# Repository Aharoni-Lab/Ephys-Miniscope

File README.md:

## Tutorial for assembling and using the integrated ephys Miniscope

Here we discuss the setup for the E-Scope. Below outlines the steps involved in assembling the head-mounted portion and DAQ portion of the system.

## Head-mounted E-Scope soldering and assembly

#### Components that need to be bought

* [Atmel ICE](https://www.digikey.com/products/en?mpart=ATATMEL-ICE&v=150) for programming the wire-free PCB
* Mill-Max 50mil male and female headers. You can get these from digikey.com and they are used to connect the INTAN PCB to the CMOS PCB. These are optional and generally should be skipped for mice.

#### Software to download
* Download [Atmel Studio](https://www.microchip.com/mplab/avr-support/atmel-studio-7). This will be used to program the microcontroller firmware onto the CMOS PCB.
* Downloaod the [Intan RHD2000 Interface Software](http://intantech.com/files/RHD2000interface_compiled_v1_5_2.zip). This will be used to connect and record ephys data.

### 1) Soldering wires to connect the CMOS PCB to the INTAN PCB

We first need to wire up 5 wires on the CMOS PCB. You should use very thing wiring for this (~0.25mm diameter conductors) since some of these connections will attach directly to the side pad of the serializer chip. You can use very thing "wire-wrap" wire which is single core or you can use mutlicore wire. Single core has the advantage of not splaying out but it is also less flexible. Once soldered, you should lay all 5 wires down across the top of the serializer and epoxy them (with a PCB safe glue/epoxy) so that no strain is applied to the solder connections. 

Below is a picture of the locations to solder the 5 wires. 
* D10 and D11 will carry the SSC Clock and SSC Data lines. 
* PCLK carries the pixel clock which will drive the SSC data protocol out of the INTAN PCB. 
* Finally, V+ and GND will provide power to the INTAN PCB.

### 2) Soldering wires onto the INTAN PCB

Now we need to solder the wires coming off the CMOS PCB onto the INTAN PCB. We have the choice to either directly solder these wires or to place a MillMax 50mil pitch header on these pads to connectorize them. For mice I would suggest directly soldering to minimize size and weight.

For connecting to the CMOS PCB v3.2 you will do the following connections (shown in the image below:
* GND connects to GND
* MCU V+ connects to V+
* INTAN V+ connects to V+
* SSC DATA connects to D10 or D11 (either is fine but keep this consistent across the E-Scopes you assemble
* LV can be left unconnected
* SSC Clock connects to PCLK
* SSC FRAME connects to D10 or D11 (use which ever one you didn't connect SSC DATA to)

### 3) Programming the MCU on the INTAN PCB

On one side of the INTAN PCB is the Intan RHD2132 chip and the other side is an ARM Cortex microcontroller (MCU). This MCU needs to be programmed once with the E-Scope firmware before it is functional. To do this we need to connect 4 lines to the INTAN PCB. This can, and maybe should, be done before completing step 2 above. The advantage of doing this programming step after completing step 2 above is the INTAN PCB can be powered through the coax cable and no additional power supply is needed.

You need to connect the following lines (refer to the images in step 2):
* SWCLK
* SWDIO
* MCU V+
* GND

These 4 lines need to be connected to an Atmel ICE which is the hardware necessary to program the MCU using an SWD protocol.
* In order to program the microcontroller on the INTAN  PCB, we first need to wire-up and connectorize a 4pin Mill-Max header to the 4 programming pins of the Atmel ICE programmer. These are GND, VTG (or V+), SWDIO, and SWDCLK. Below shows which pins/wires of the Atmel ICE have which function. The Atmel ICE has 2 different 5x2 pin ports. One is labeled AVR and one is labeled SAM. Either will work but depending on which one you are using it will change which column you refer to in the below chart.

* Connect the Atmel ICE to the programming header of the INTAN PCB.
* Power up the INTAN PCB throught either the coax cable (using the Miniscope DAQ) or directly connect 3.3V and GND from a power supply to the V+ and GND pads. 
* When the INTAN PCB gets powered on, you should see an orange light turn on on the Atmel ICE which shows that the Atmel ICE has detected voltage on the VTG (Voltage Target) pin.
* Open Atmel Studio and click the "Device Programming" button

* In the Device Programming window that pops up select:
  * Tool: Atmel ICE
  * Device: ATSAM....
  * Interface: SWD
  * Then click "Apply"
* Now check to make sure that Atmel Studio can communicate with the microcontroller on the INTAN PCB. You do this by clicking the "Read" button under Device Signature. If everything is powered and connected correctly you should see some numbers and letter pop up in the box and no error window show up. Now we are ready to program the microcontroller.
* Exit the Device Programming window.
* Now we have to do something a bit weird. I am not sure why this has to be done but it does. Open up the Atmel project found in the "/E-Scope-firmware" folder. This load up the code that makes up the INTAN MCU firmware. Now click "Debug" from the top menu bar and then click "Start Debugging and Break". Wait about 15 seconds while the debugger does its thing in Atmel Studio and then the code should jump to the "main()" function and highlight it. Now click the play button (labelled "Start Debugging") in the top menu. Wait a few seconds then click the stop button (labelled "Stop Debugging"). 
* Go back to the "Device Programming" window by clicking the "Device Programming" button.
* Click "Memory" on the left menu panel of the Device Programming window we are currently in.
* Click "Browse" and locate the E-Scope firmware. This is a .hex file you can find in the "/E-Scope-firmware" folder.
* Click "Program". This will erase, program, and verify the microcontroller. It will tell you if everything was successful.
* Now the microcontroller on the INTAN PCB knows how to be a wire-free Miniscope microcontroller.

## Miniscope DAQ E-Scope soldering and assembly

We now need to modify the standard Miniscope DAQ to be able to handle and transmit the ephys data from the E-Scope. We will do this by soldering 4 wires onto the DAQ PCB which will send the ephys data from the Miniscope DAQ to our SSC to INTAN LVDS PCB. We will roughly be following the following schematic:

As you can see from the schematic, these wires coming off of the Miniscope DAQ PCB will connect to hardware that basically undoes the SSC data protocol implemented by the MCU on the INTAN PCB and make an Intan DAQ think that it is talking directly to an Intan headstage.

### 1) Wire up the Miniscope DAQ PCB

Similar to what we did for wiring up the CMOS PCB, we need to wire up some lines for SSC DATA, SSC Clock, SSC FRAME, and power. See image below for which pads to solder to. Use the same wire as you used to wire up the CMOS PCB and epoxy these wires down to the DAQ PCB to remove any strain on the solder joints.

You definitely need to solder up D10, D11, PCLK, and GND. The need for the 3.3V connection will depend on which version of the system you are using. You might as well just solder this one up as well.

### 2) Change the Miniscope DAQ Deserializer Mode from 10 bits to 12 bits

We need to remove one resistor on the Miniscope PCB and short then now empty pads together . This resistor is responsible for change the Deserializer from using 10bit mode to 12bit mode. We need to do this because the CMOS imaging sensor uses the bottom 10 bits of the SERDES and the Ephys data uses the top 2 bits (TD, TF which are on pins D10 and D11). So **remove resistor R46 (which is circled in yellow above)** which is near the top of the PCB to the right of the SMA connector that goes to the head-mounted scope. Once you remove this resistor, we need to short the 2 open pads together which effectively changes this resistance to 0 ohms. You can build up a solder ball that spans these 2 pads, solder a short piece of metal across these 2 pads, or solder a 0ohm resistor in the R46 location. I recommend the last option.

### 3) Connect the Miniscope DAQ PCB to SSC-2-INTAN-LVDS PCB

Alright, we are almost done here. The ephys data coming out of the wires we soldered onto the Miniscope DAQ need to get converted to a data protocol an Intan DAQ understands. We do this using our custom SSC-2-INTAN-LVDS PCB. This PCB receives SSC (RF,RT,RK) and converts it to an LVDS SPI to be sent out over a 2x6 omnetics connector at the top of the PCB to an Intan or OpenEphys DAQ. Below is a rendering of this PCB.

At the bottom of this board is a 5 pin 100mil pitch header for connecting it to the Miniscope DAQ. I would suggest soldering a right angle header to this PCB pointing down. On the Miniscope DAQ, you can epoxy another 5 pin header to the edge of the PCB so that these 2 PCBs can be easily connected. The connections need to be the following:

**NOTE**

**For the original version of this PCB, the labelling is incorrect.** The order should 3.3V, RD, RF, RK, GND and not 3.3V, RK, RD, RF, GND.

| SSC-2-INTAN PCB | Miniscope DAQ PCB |
| --- | --- |
| GND | GND |
| 3.3V | 3.3V |
| RK | PCLK |
| RD | D10 or D11. Whichever one was connected to TD on the 32 channel Ephys PCB|
| RF | D10 or D11. Whichever one was connected to TF on the 32 channel Ephys PCB |

### 4) Program the MCU on the SSC-2-INTAN-LVDS PCB

Out last step is to program this PCB so it knows what it is suppose to do. Here we follow the same procedure we did above for programming the 32 Channel Ephys PCB. The programming header on the SSC-2-INTAN-LVDS PCB is on the left and includes the 4 connections you need access to through a 100mil pitch header. These are VTG (which will tell the Atmel ICE programmer to program the MCU at 3.3V), SWDIO, SWCLK, and GDN. Follow the steps above but program this MCU with the SSC-2-INTAN-LVDS firmware .hex file. This PCB needs to be powered up when programming which is done through the bottom 'MS-DAQ' 5 pin header by supplying 3.3V and GND. If you already have this hooked up to the Miniscope DAQ all you should need to do is power up the Miniscope DAQ and it should in turn power on this PCB.

## Hook everything up and test the system

We should now be done with all the hard work. All that is left to do is connect everything together and make sure we are getting correct data from the system. The overall layout should be:

32 Channel Ephys PCB -> CMOS sensor PCB -> coax -> Miniscope DAQ -> SSC-2-INTAN-LVDS PCB -> Intan or Open Ephys DAQ

All the power on all of these PCBs is floating which apperently introduces a ton of noise. **To fix this we need to connect building ground to the ground of the Miniscope system. This can be most easily done (be careful) by plugging in only the ground pin of an electrical cord into a wall electical socket and then clip the other end of the ground wire of the cable to the pin labeled 'GND' on the SSC-2-INTAN-LVDS PCB. Do this before powering everything up.**

Once you have connected building ground you can plug in the USB cable of the Miniscope DAQ and the USB cable and power jack of the Intan DAQ. Now open up the Intan DAQ software on the computer and make sure it detects the Intan DAQ and a 32 channel headstage. Right now the Intan DAQ thinks it is talking to an Intan headstage but it is actually talking to the SSC-2-INTAN-LVDS PCB. If you leave the coax cable unconnected from the Miniscope DAQ you will see placeholder data show up in the Intan DAQ software. This should look like DC voltages on all 32 channels with channel 0 having the lowest voltage and channel 31 having the highests. Once the head-mounted Miniscope coax cable is connected, this placeholder data gets replaced with real ephys data.

**A few important notes:**

* Generally you will want the ephys and imaging synced together. This is done by connecting one of the Intan DAQ digital input ports to the SYNC output of the Miniscope DAQ (which is the SMA connector labeled J5). Make sure to enable this digitial input pin in the Intan DAQ software. This will result in the Intan DAQ recording the SYNC signal from the Miniscope DAQ which will allow us to sync all the data offline. If you do this, **make sure to always start the Intan DAQ software recordinging before you start the Miniscope DAQ software recording.**

**Order of connecting and powering up the system**

* Hook up ground of the DAQ system to building ground
* Connect the Miniscope to Miniscope DAQ using the coax cable
* Hook up the DC power supply on the Intan DAQ
* Hook up the two USB cables. One for the Miniscope DAQ and one for the Intan DAQ
* Make sure that the sync cable is connected (Cable that connects the Intan board with the Miniscope DAQ)
* Open up Intan DAQ software and Miniscope DAQ software
* In the Intan software, click "Board Digital Inputs" radio button. Then turn on LOGIC DIN-00.
* Check everything is running correctly by clicking the "Runn" button in the Intan software and by connecting to the Miniscope using the Miniscope DAQ software.

**When ready to record**
* In the Intan software, click the "Select Vase Filename" button and name the ephys recording file.
* Click record in the Intan software
* Click record in the Miniscope DAQ software
* Do your recording
* Stop recording with the Miniscope DAQ software
* Stop recording with the Intan software

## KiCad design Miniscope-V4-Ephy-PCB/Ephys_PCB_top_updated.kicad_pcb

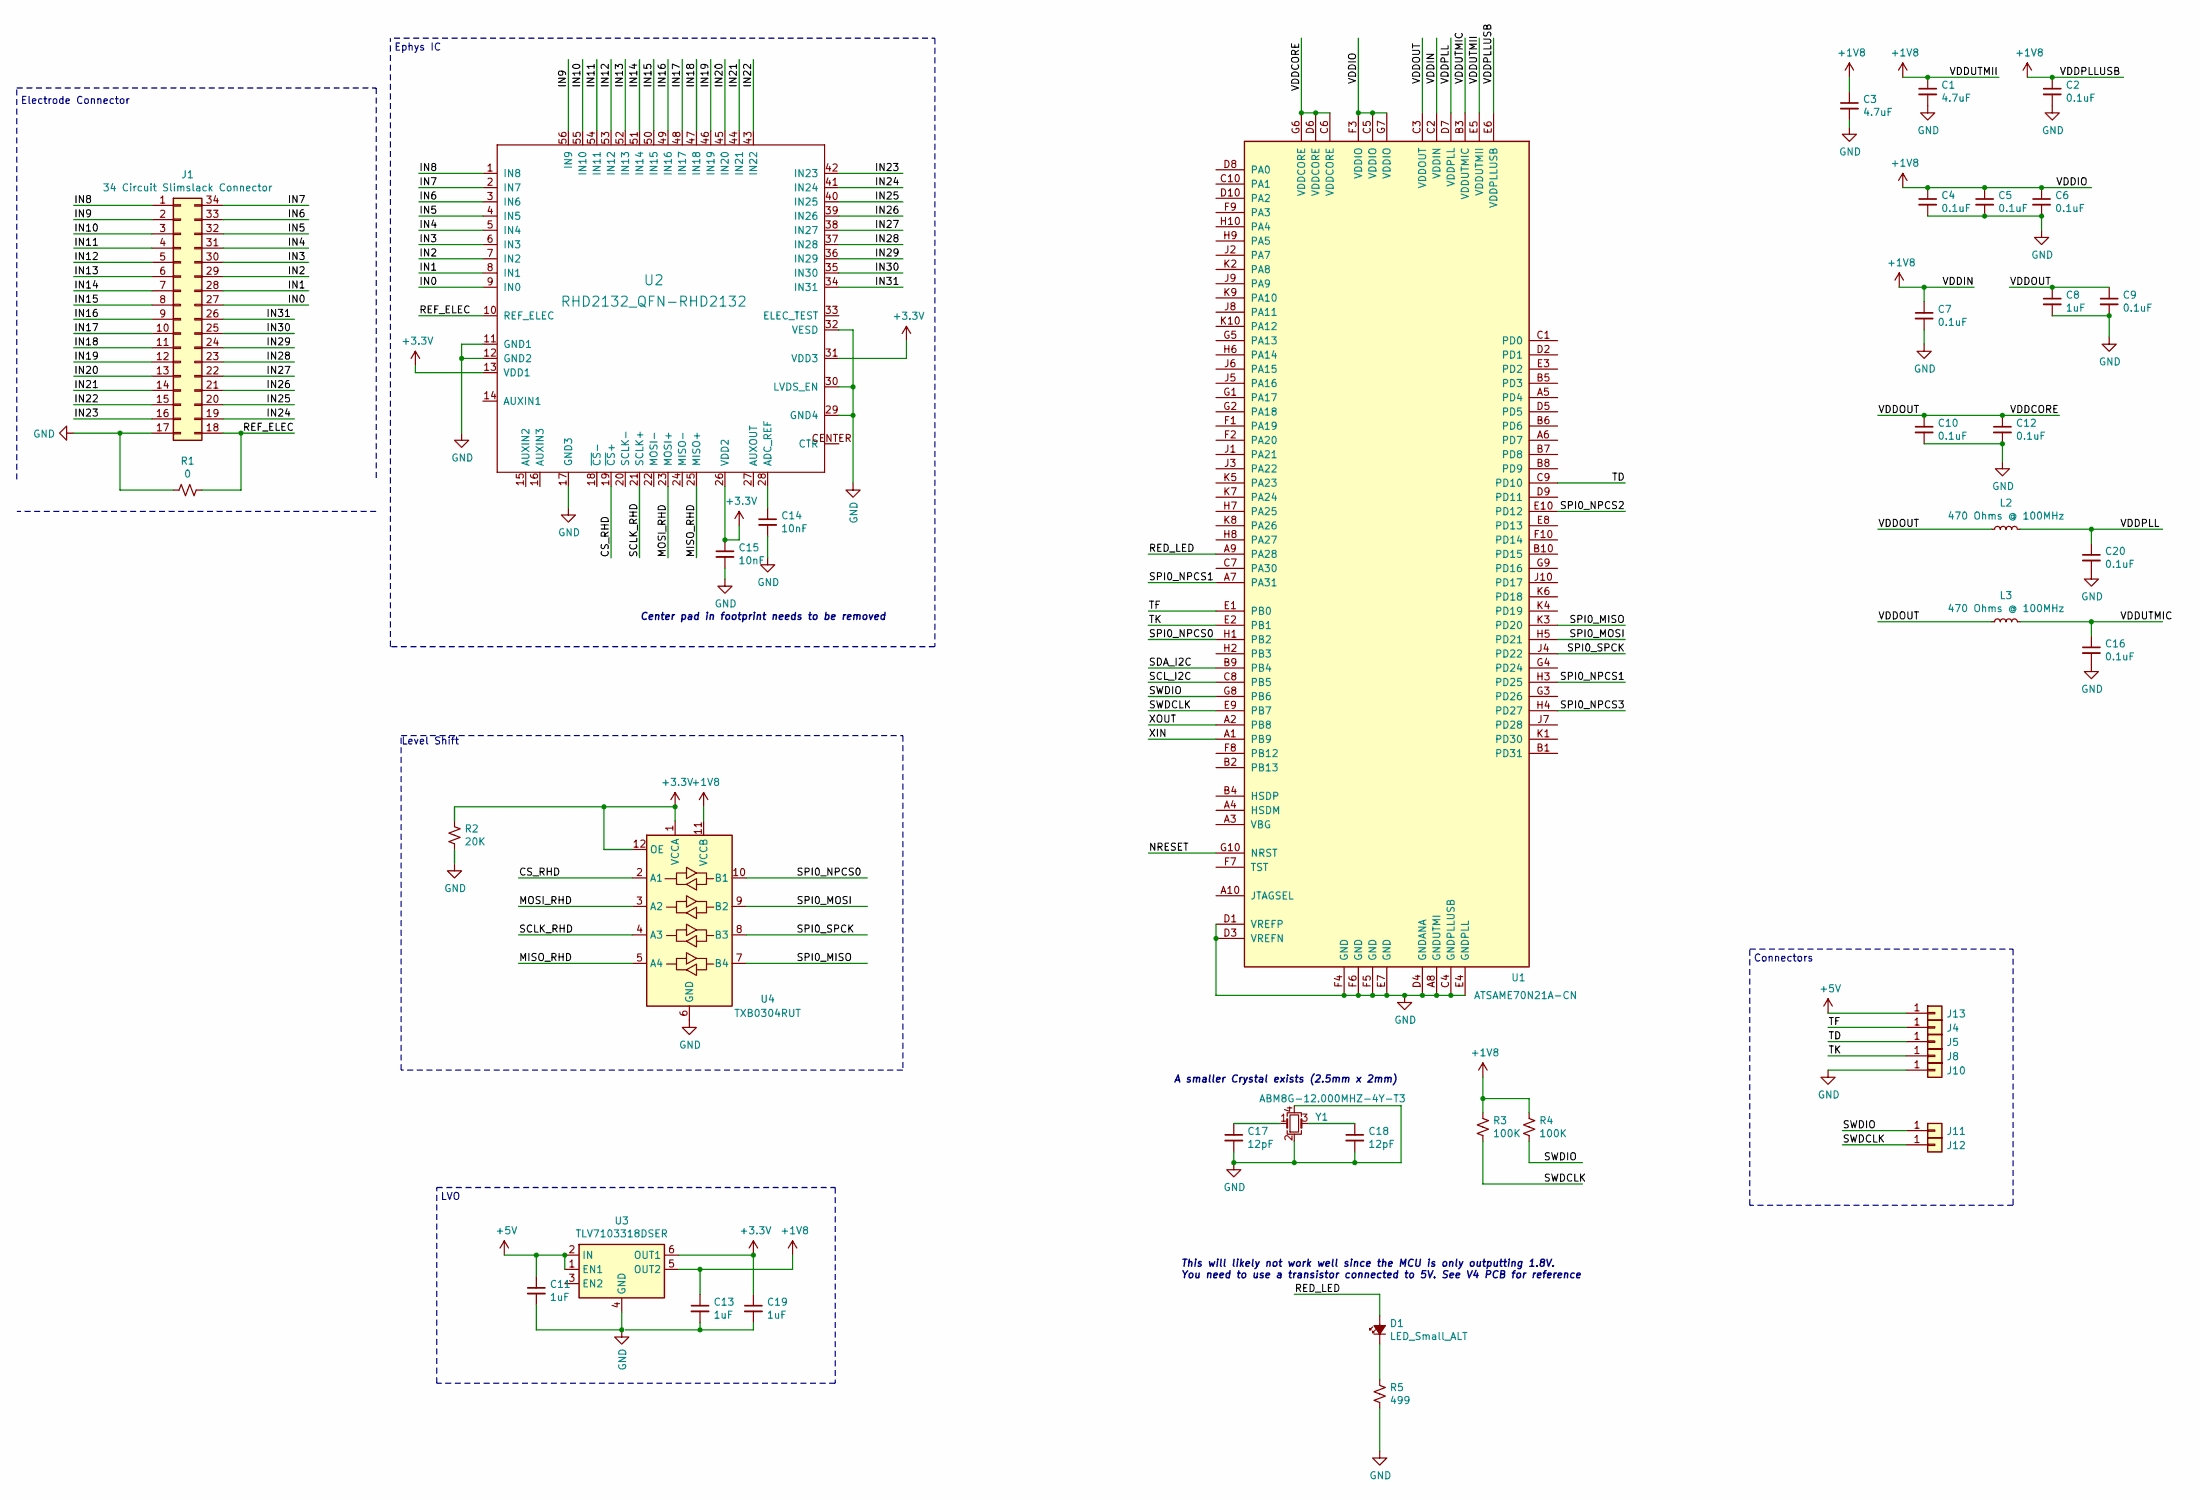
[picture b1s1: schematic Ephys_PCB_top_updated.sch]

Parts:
C1, C3: 4.7uF; C_0402_1005Metric_L
C2, C4, C5, C6, C7, C9, C10, C12, C16, C20: GRM033R61A104ME15D; C_0201_0603Metric
C8, C11, C13, C17, C18, C19: GRM033R60J105MEA2D; C_0201_0603Metric
C14, C15: GRM033R71A103KA01D; C_0201_0603Metric
D1: LED_Small_ALT; LED_0402_1005Metric
J1: 34 Circuit Slimslack Connector; SS_5046223412
J4, J5, J8, J10, J11, J12, J13: Conn_01x01; TestPoint_Pad_1.0x1.0mm
L2, L3: BLM18PG471SN1D; L_0603_1608Metric
R1: 0; R_0201_0603Metric_ERJ_L
R2: 20K; R_0201_0603Metric_ERJ_L
R3, R4: 100K; R_0201_0603Metric_ERJ_L
R5: 499; R_0201_0603Metric_ERJ_L
U1: ATSAME70N21A-CN; BGA_100_CP80_10X10_900X900X110B40L
U2: RHD2132_QFN-RHD2132; QFN-56-1EP_8x8mm_P0.5mm_EP5.6x5.6mm
U3: TLV7103318DSER; SON_6_P50_150X150X80L50X25L
U4: TXB0304RUT; Texas_R_PUQFN-N12
Y1: ABM8G-12.000MHZ-4Y-T3; OSCCC320X250X100L80X100

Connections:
+1V8: C1.1, C2.1, C3.1, C4.1, C5.1, C6.1, C7.1, C13.1, R3.1, R4.1, U1.C2 (VDDIN), U1.C5 (VDDIO), U1.E5 (VDDUTMII), U1.E6 (VDDPLLUSB), U1.F3 (VDDIO), U1.G7 (VDDIO), U3.5 (OUT2), U4.11 (VCCB)
+3V3: C15.1, C19.1, R2.2, U2.13 (VDD1), U2.26 (VDD2), U2.31 (VDD3), U3.6 (OUT1), U4.1 (VCCA), U4.12 (OE)
+5V: C11.1, J13.1, U3.1 (EN1), U3.2 (IN)
/CS_RHD: U2.19 (~CS~+), U4.2 (A1)
/IN0: J1.27, U2.9 (IN0)
/IN1: J1.28, U2.8 (IN1)
/IN2: J1.29, U2.7 (IN2)
/IN3: J1.30, U2.6 (IN3)
/IN4: J1.31, U2.5 (IN4)
/IN5: J1.32, U2.4 (IN5)
/IN6: J1.33, U2.3 (IN6)
/IN7: J1.34, U2.2 (IN7)
/IN8: J1.1, U2.1 (IN8)
/IN9: J1.2, U2.56 (IN9)
/IN10: J1.3, U2.55 (IN10)
/IN11: J1.4, U2.54 (IN11)
/IN12: J1.5, U2.53 (IN12)
/IN13: J1.6, U2.52 (IN13)
/IN14: J1.7, U2.51 (IN14)
/IN15: J1.8, U2.50 (IN15)
/IN16: J1.9, U2.49 (IN16)
/IN17: J1.10, U2.48 (IN17)
/IN18: J1.11, U2.47 (IN18)
/IN19: J1.12, U2.46 (IN19)
/IN20: J1.13, U2.45 (IN20)
/IN21: J1.14, U2.44 (IN21)
/IN22: J1.15, U2.43 (IN22)
/IN23: J1.16, U2.42 (IN23)
/IN24: J1.19, U2.41 (IN24)
/IN25: J1.20, U2.40 (IN25)
/IN26: J1.21, U2.39 (IN26)
/IN27: J1.22, U2.38 (IN27)
/IN28: J1.23, U2.37 (IN28)
/IN29: J1.24, U2.36 (IN29)
/IN30: J1.25, U2.35 (IN30)
/IN31: J1.26, U2.34 (IN31)
/MISO_RHD: U2.25 (MISO+), U4.5 (A4)
/MOSI_RHD: U2.23 (MOSI+), U4.3 (A2)
/NRESET: U1.G10 (NRST)
/RED_LED: D1.2 (A), U1.A9 (PA28)
/REF_ELEC: J1.18, R1.1, U2.10 (REF_ELEC)
/SCLK_RHD: U2.21 (SCLK+), U4.4 (A3)
/SCL_I2C: U1.C8 (PB5)
/SDA_I2C: U1.B9 (PB4)
/SPI0_MISO: U1.K3 (PD20), U4.7 (B4)
/SPI0_MOSI: U1.H5 (PD21), U4.9 (B2)
/SPI0_NPCS0: U1.H1 (PB2), U4.10 (B1)
/SPI0_NPCS1: U1.A7 (PA31), U1.H3 (PD25)
/SPI0_NPCS2: U1.E10 (PD12)
/SPI0_NPCS3: U1.H4 (PD27)
/SPI0_SPCK: U1.J4 (PD22), U4.8 (B3)
/SWDCLK: J12.1, R3.2, U1.E9 (PB7)
/SWDIO: J11.1, R4.2, U1.G8 (PB6)
/TD: J5.1, U1.C9 (PD10)
/TF: J4.1, U1.E1 (PB0)
/TK: J8.1, U1.E2 (PB1)
/VDDCORE: C8.1, C9.1, C10.1, C12.1, L2.1, L3.1, U1.C3 (VDDOUT), U1.C6 (VDDCORE), U1.D6 (VDDCORE), U1.G6 (VDDCORE)
/VDDPLL: C20.1, L2.2, U1.D7 (VDDPLL)
/VDDUTMIC: C16.1, L3.2, U1.B3 (VDDUTMIC)
/XIN: U1.A1 (PB9)
/XOUT: U1.A2 (PB8)
GND: C1.2, C2.2, C3.2, C4.2, C5.2, C6.2, C7.2, C8.2, C9.2, C10.2, C11.2, C12.2, C14.2, C15.2, C16.2, C17.2, C18.2, C20.2, J1.17, J10.1, R1.2, R2.1, R5.2, U1.A8 (GNDUTMI), U1.C4 (GNDPLLUSB), U1.D1 (VREFP), U1.D3 (VREFN), U1.D4 (GNDANA), U1.E4 (GNDPLL), U1.E7 (GND), U1.F4 (GND), U1.F5 (GND), U1.F6 (GND), U2.11 (GND1), U2.12 (GND2), U2.17 (GND3), U2.29 (GND4), U2.30 (LVDS_EN), U2.32 (VESD), U3.4 (GND), U4.6 (GND), Y1.2, Y1.4
unnamed: C13.2, C19.2
unnamed: C14.1, U2.28 (ADC_REF)
unnamed: C17.1, Y1.1
unnamed: C18.1, Y1.3
unnamed: D1.1 (K), R5.1

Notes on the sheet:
Center pad in footprint needs to be removed
This will likely not work well since the MCU is only outputting 1.8V. You need to use a transistor connected to 5V. See V4 PCB for reference
LVO
Level Shift
Electrode Connector
Ephys IC
Connectors
A smaller Crystal exists (2.5mm x 2mm)

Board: 6 copper layers, 41 parts (4 on the bottom side), 60 nets, no tracks yet.

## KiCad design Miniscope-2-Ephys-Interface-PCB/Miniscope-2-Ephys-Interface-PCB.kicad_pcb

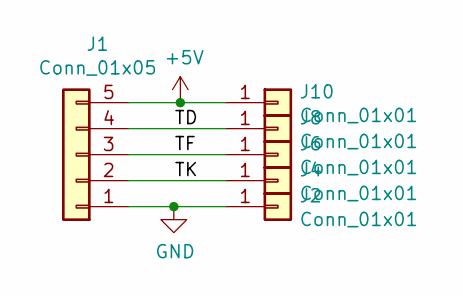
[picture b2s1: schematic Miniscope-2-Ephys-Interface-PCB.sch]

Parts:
J1: Conn_01x05; B2B_Flex_05_Dual_Row_38milx24mil_Hole_20mil_small
J2, J4, J6, J8, J10: Conn_01x01; Spring_2306654_3

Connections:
+5V: J1.5, J10.1
/TD: J1.4, J8.1
/TF: J1.3, J6.1
/TK: J1.2, J4.1
GND: J1.1, J2.1

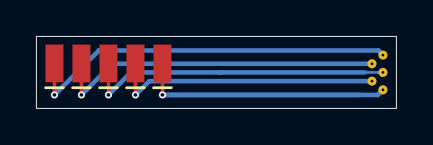
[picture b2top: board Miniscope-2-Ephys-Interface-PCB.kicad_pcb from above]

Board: 2 copper layers, 20.0 x 4.0 mm, 6 parts (0 on the bottom side), 5 nets.

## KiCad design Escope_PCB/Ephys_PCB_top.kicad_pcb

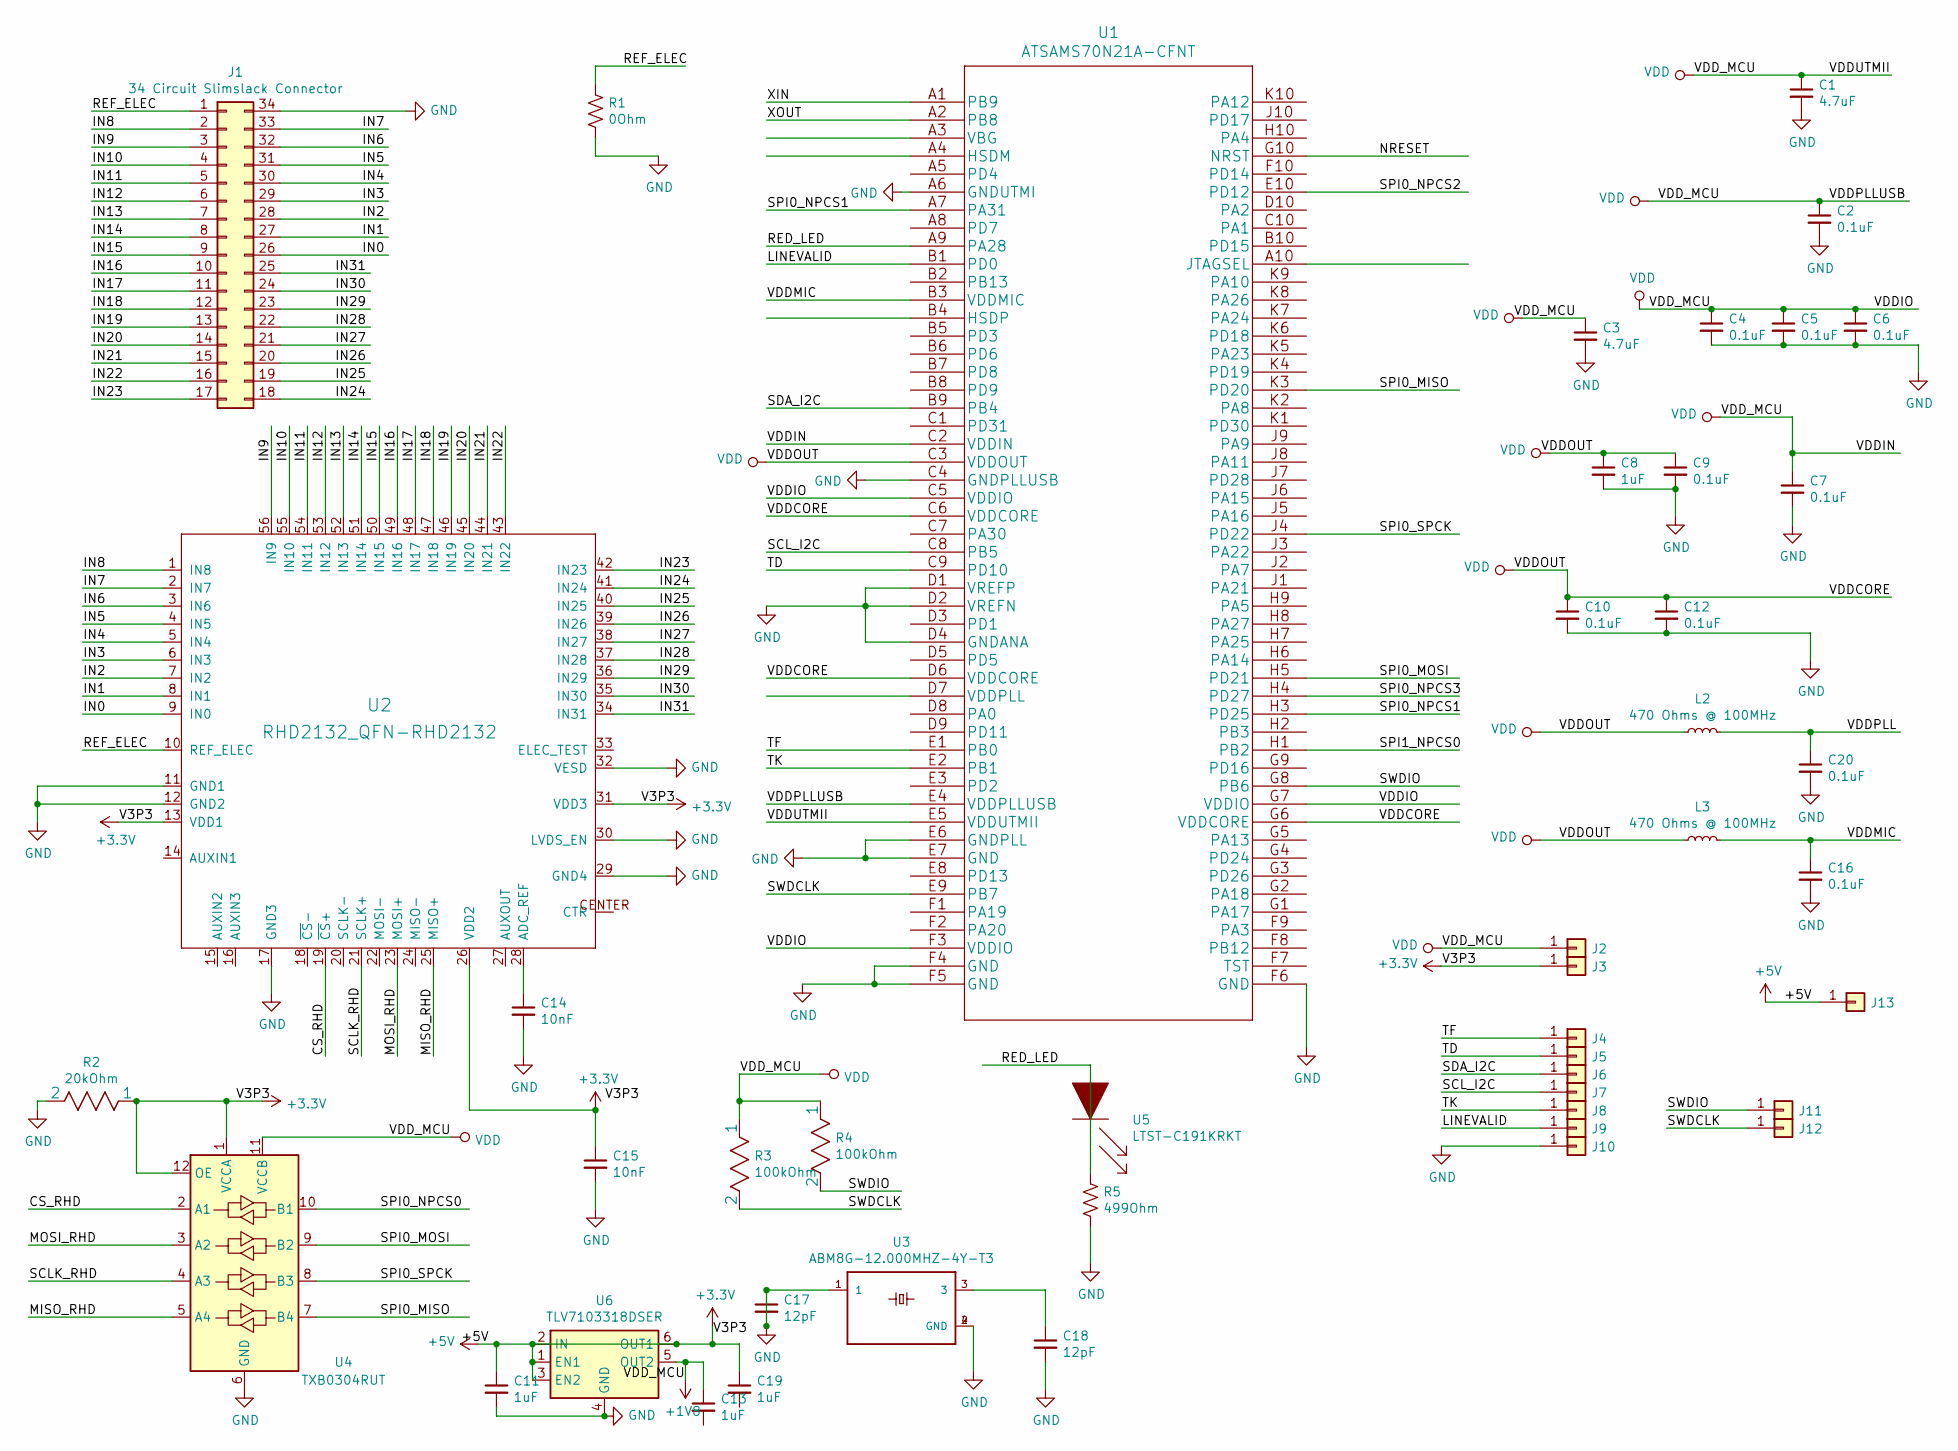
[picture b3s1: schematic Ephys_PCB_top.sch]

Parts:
C1, C3: GRM155R60J475ME87D; GRM155R60J475ME47D
C2, C4, C5, C6, C7, C9, C10, C12, C16, C20: GRM033R61A104ME15D; C_0201_0603Metric
C8, C11, C13, C19: GRM033R60J105MEA2D; C_0201_0603Metric
C14, C15: GRM033R71A103KA01D; C_0201_0603Metric
C17, C18: GRM1555C1H120JA01D; C_01005_0402Metric
J1: 34 Circuit Slimslack Connector; Molex_SlimStack_55560-0341_2x17_P0.50mm_Vertical
J2, J3, J4, J5, J6, J8, J9, J10, J11, J12, J13: Conn_01x01; TestPoint_Pad_1.0x1.0mm
J7: TestPoint_Pad_1.0x1.0mm
L2, L3: BLM18PG471SN1D; L_0603_1608Metric
R1: 0Ohm; ERJ-1GEF1003C
R2: 20kOhm; ERJ-1GEF2002C
R3, R4: 100kOhm; ERJ-1GEF1003C
R5: 499Ohm; ERJ-1GEF1003C
U1: ATSAMS70N21A-CFNT
U2: RHD2132_QFN-RHD2132; QFN-56-1EP_8x8mm_P0.5mm_EP5.6x5.6mm
U3: ABM8G-12.000MHZ-4Y-T3; OSCSC320X250X100N
U4: TXB0304RUT; Texas_R_PUQFN-N12
U5: LTST-C191KRKT; LED_0402_1005Metric
U6: TLV7103318DSER; SON_6_P50_150X150X80L50X25L

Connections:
/CS_RHD: U2.19 (~CS~+), U4.2 (A1)
/IN0: J1.26, U2.9 (IN0)
/IN1: J1.27, U2.8 (IN1)
/IN2: J1.28, U2.7 (IN2)
/IN3: J1.29, U2.6 (IN3)
/IN4: J1.30, U2.5 (IN4)
/IN5: J1.31, U2.4 (IN5)
/IN6: J1.32, U2.3 (IN6)
/IN7: J1.33, U2.2 (IN7)
/IN8: J1.2, U2.1 (IN8)
/IN9: J1.3, U2.56 (IN9)
/IN10: J1.4, U2.55 (IN10)
/IN11: J1.5, U2.54 (IN11)
/IN12: J1.6, U2.53 (IN12)
/IN13: J1.7, U2.52 (IN13)
/IN14: J1.8, U2.51 (IN14)
/IN15: J1.9, U2.50 (IN15)
/IN16: J1.10, U2.49 (IN16)
/IN17: J1.11, U2.48 (IN17)
/IN18: J1.12, U2.47 (IN18)
/IN19: J1.13, U2.46 (IN19)
/IN20: J1.14, U2.45 (IN20)
/IN21: J1.15, U2.44 (IN21)
/IN22: J1.16, U2.43 (IN22)
/IN23: J1.17, U2.42 (IN23)
/IN24: J1.18, U2.41 (IN24)
/IN25: J1.19, U2.40 (IN25)
/IN26: J1.20, U2.39 (IN26)
/IN27: J1.21, U2.38 (IN27)
/IN28: J1.22, U2.37 (IN28)
/IN29: J1.23, U2.36 (IN29)
/IN30: J1.24, U2.35 (IN30)
/IN31: J1.25, U2.34 (IN31)
/LINEVALID: J9.1, U1.B1 (PD0)
/MISO_RHD: U2.25 (MISO+), U4.5 (A4)
/MOSI_RHD: U2.23 (MOSI+), U4.3 (A2)
/NRESET: U1.G10 (NRST)
/RED_LED: R5.1, U1.A9 (PA28)
/REF_ELEC: J1.1, R1.1, U2.10 (REF_ELEC)
/SCLK_RHD: U2.21 (SCLK+), U4.4 (A3)
/SCL_I2C: J7.1, U1.C8 (PB5)
/SDA_I2C: J6.1, U1.B9 (PB4)
/SPI0_MISO: U1.K3 (PD20), U4.7 (B4)
/SPI0_MOSI: U1.H5 (PD21), U4.9 (B2)
/SPI0_NPCS0: U4.10 (B1)
/SPI0_NPCS1: U1.A7 (PA31), U1.H3 (PD25)
/SPI0_NPCS2: U1.E10 (PD12)
/SPI0_NPCS3: U1.H4 (PD27)
/SPI0_SPCK: U1.J4 (PD22), U4.8 (B3)
/SPI1_NPCS0: U1.H1 (PB2)
/SWDCLK: J12.1, R3.2, U1.E9 (PB7)
/SWDIO: J11.1, R4.2, U1.G8 (PB6)
/TD: J5.1, U1.C9 (PD10)
/TF: J4.1, U1.E1 (PB0)
/TK: J8.1, U1.E2 (PB1)
/VDDMIC: C16.1, L3.2, U1.B3 (VDDMIC)
/VDDPLL: C20.1, L2.2
/XIN: U1.A1 (PB9)
/XOUT: U1.A2 (PB8)
unnamed: C14.1, U2.28 (ADC_REF)
unnamed: C18.1, U3.3

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
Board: 2 copper layers, 46 parts (0 on the bottom side), 59 nets, no tracks yet.

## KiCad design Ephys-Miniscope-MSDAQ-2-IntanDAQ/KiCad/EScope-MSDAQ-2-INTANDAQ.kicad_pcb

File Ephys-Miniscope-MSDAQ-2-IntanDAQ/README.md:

# Ephys-Miniscope-MSDAQ-2-IntanDAQ

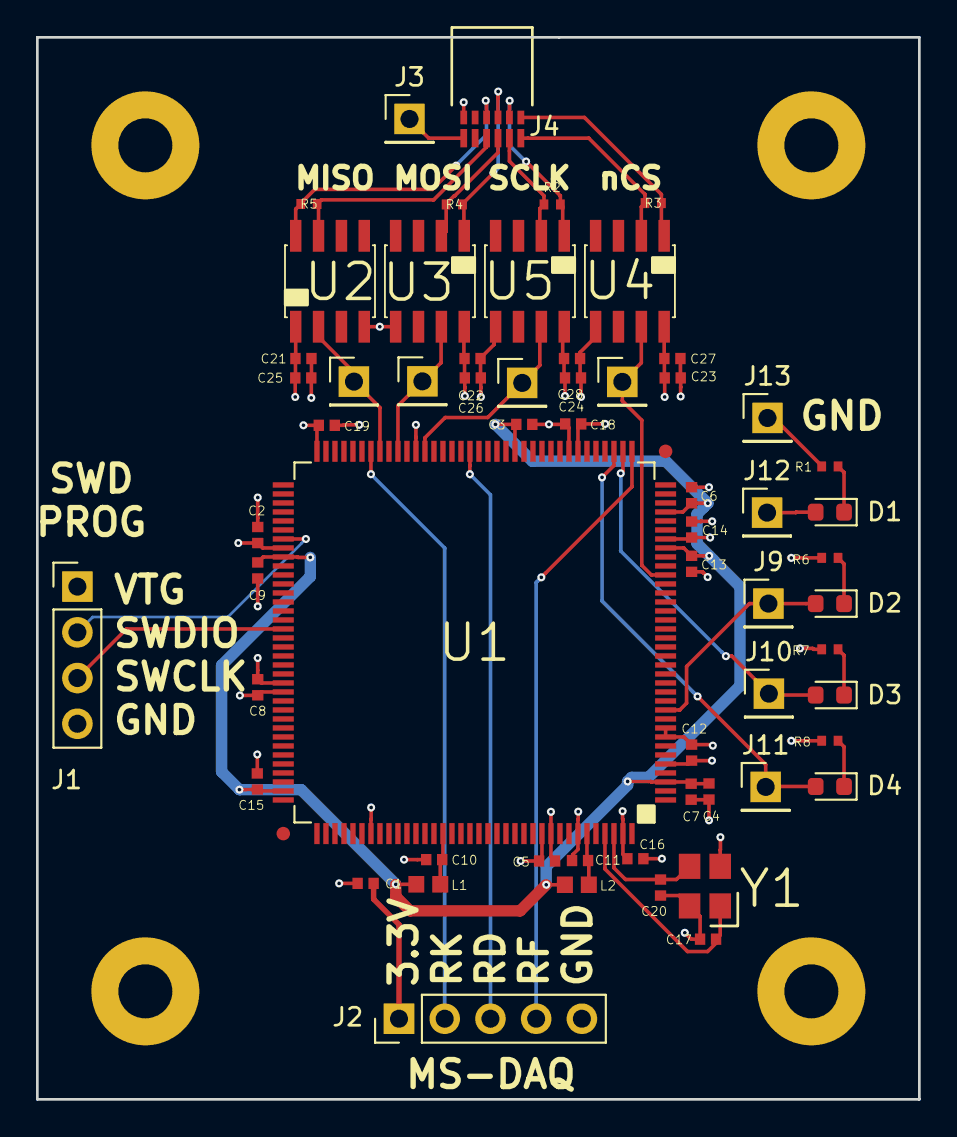
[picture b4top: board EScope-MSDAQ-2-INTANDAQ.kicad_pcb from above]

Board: 4 copper layers, 49.0 x 59.0 mm, 65 parts (0 on the bottom side), 32 nets.

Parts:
C1: GRM155R60J106ME15D; C_0402_1005Metric_L
C2, C3, C5, C6, C7, C8, C9, C10, C11, C12, C13, C14, C15, C16, C18, C19, C21, C22, C23, C24: GRM155R71A104JA01D; C_0402_1005Metric_L
C4: GRM155R60J225KE95D; C_0402_1005Metric_L
C17, C20: GRM1555C1H120JA01D; C_0402_1005Metric_L
C25, C26, C27, C28: GRM155R71H102KA01D; C_0402_1005Metric_L
D1, D2, D3, D4: LED_Small_ALT; LED_0603_1608Metric
H1, H2, H3, H4: MountingHole_Pad; MountingHole_3mm_Pad
J1: Conn_01x04; PinHeader_1x04_P2.54mm_Vertical
J2: Conn_01x05; PinHeader_1x05_P2.54mm_Vertical
J3, J5, J6, J7, J8, J9, J10, J11, J12, J13: Conn_01x01; PinHeader_1x01_P2.54mm_Vertical
J4: A79623-001
L1, L2: BLM18PG471SN1D; L_0603_1608Metric_L
R1, R2, R3, R4, R5, R6, R7, R8: ERJ-2RKF1000X; R_0402_1005Metric_ERJ_L
U1: ATSAMV71Q21B-AABT; QFP_144_P50_2200X2200X160L60X22N
U2: DS90LV017A; SOIC_8_P127_490X600X175L83X41L
U3, U4, U5: DS90LV018A; SOIC_8_P127_490X600X175L83X41L
Y1: ABM8G-12.000MHZ-4Y-T3; OSCCC320X250X100L80X100

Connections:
+3V3: C1.1, C2.1, C5.1, C8.1, C12.1, C14.1, C16.1, C18.1, C19.1, C21.2, C22.1, C23.1, C24.1, C25.2, C26.1, C27.1, C28.1, D1.2, J1.1, J2.1, J12.1, U1.5, U1.30, U1.43, U1.72, U1.80, U1.96, U1.134, U1.143, U2.1, U3.8, U4.8, U5.8
/LED1: D2.2, J9.1, U1.11
/LED2: D3.2, J10.1, U1.38
/LED3: D4.2, J11.1, U1.39
/MCU_SPI_MISO: J8.1, U1.65, U2.2
/MCU_SPI_MOSI: J5.1, U1.63, U3.7
/MCU_SPI_NPCS: J6.1, U1.26, U4.7
/MCU_SPI_SPCK: J7.1, U1.60, U5.7
/MISO+: J4.7, R5.1, U2.7
/MISO-: J4.8, R5.2, U2.8
/MOSI+: J4.5, R4.2, U3.2
/MOSI-: J4.6, R4.1, U3.1
/RD: J2.2, U1.66
/RF: J2.3, U1.55
/RK: J2.4, U1.37
/SCLK+: J4.3, R2.2, U5.2
/SCLK-: J4.4, R2.1, U5.1
/SWCLK: J1.3, U1.89
/SWDIO: J1.2, U1.79
/VDDCORE: C3.1, C4.1, C6.1, C7.1, C9.1, C13.1, C15.1, L1.2, L2.2, U1.3, U1.29, U1.33, U1.50, U1.81, U1.107
/VDDPLL: C10.1, L1.1, U1.123
/VDDUTMIC: C11.1, L2.1, U1.139
/XIN: C17.1, U1.141, Y1.1
/XOUT: C20.1, U1.142, Y1.3
/nCS+: J4.1, R3.2, U4.2
/nCS-: J4.2, R3.1, U4.1
GND: C1.2, C2.2, C3.2, C4.2, C5.2, C6.2, C7.2, C8.2, C9.2, C10.2, C11.2, C12.2, C13.2, C14.2, C15.2, C16.2, C17.2, C18.2, C19.2, C20.2, C21.1, C22.2, C23.2, C24.2, C25.1, C26.2, C27.2, C28.2, H1.1, H2.1, H3.1, H4.1, J1.4, J2.5, J4.12, J13.1, R1.1, R6.1, R7.1, R8.1, U1.8, U1.9, U1.44, U1.61, U1.95, U1.115, U1.135, U1.138, U2.4, U3.5, U4.5, U5.5, Y1.2, Y1.4
unnamed: D1.1, R1.2
unnamed: D2.1, R6.2
unnamed: D3.1, R7.2
unnamed: D4.1, R8.2
unnamed: J3.1, J4.11

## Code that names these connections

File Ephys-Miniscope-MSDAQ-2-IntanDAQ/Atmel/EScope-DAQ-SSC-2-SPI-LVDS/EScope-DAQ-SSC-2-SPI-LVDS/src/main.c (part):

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#define RHD_READ_BIT						0x4000

// ------- LEDs on Board
#define LED1_PIN			PIO_PC0_IDX
#define LED2_PIN			PIO_PC1_IDX
#define LED3_PIN			PIO_PC2_IDX
// ------- SSC Definitions
#define RD_PIN				PIO_PA10_IDX
#define RD_MODE				IOPORT_MODE_MUX_C
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	
	sysclk_init();
	board_init();
	ioport_set_pin_dir(LED1_PIN,IOPORT_DIR_OUTPUT);
	ioport_set_pin_level(LED1_PIN, 1);
	
	irq_initialize_vectors();
	cpu_irq_enable();
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
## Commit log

2019-02-27 Add initial files
    Porting Ephys Miniscope SSC 2 LVDS SPI over from a separate git repo.
2019-02-27 Port Escope MCU code to repo
2019-03-19 Correct SWD pin labels in pictures
2019-04-24 Add .hex, .elf, and Release folder to the git repo
2019-06-27 Add 32ch silicone probe channel mapping.
2020-06-09 Create gitkeep
2020-06-09 Create gitgit
2020-06-11 Rearrange project and edit schematic with some corrections and notes.
2020-06-13 Update schematic and footprints
    * Replaced MCU symbol, pinout, and footprint with correct one (TFBGA version).
    * Created and replaced slimstack connector with the correct one.
    * Replaced crystal oscillator with better symbol
    * Tried to link as many footprints as possible to those contained in the Aharoni KiCad Library.
    * TODO: Add transistor to drive status LED.
2020-06-13 Group components in PCB layout
2020-06-13 Update Board Setup Specifications
    Via: 0.15mm/0,3mm
    Trace/Space: 3mil/3mil
2020-06-13 Switch to 6 layer PCB
2020-06-13 Move things around in PCBnew and add prelim board outline.
2020-06-14 Add a prototype Miniscope to Ephys PCB connector PCB
2020-06-14 Change display layers for designators and footprint info.
2020-06-14 Move around PCB layout a bit and initial route of electrode traces.
2020-06-15 Move to new KiCad project for multi-board Ephys layout
2020-06-15 Finish initial PCB layout.
2020-06-15 Finish layout of MCU PCB and routing of almost all traces.
2020-06-15 Change orientation of some components and add notes to PCB layout
2020-06-16 Switch to female slimstack and reorder pins to batch 32ch silicon probe connector
2020-06-16 Finish routing Ephys and Connector PCBs. Decrease layer count to 4.
2020-06-16 Finish routing of all PCBs. Need to double check before fabrication.
2020-06-26 Revert "pcb file updated"
2020-06-30 Add mouse bites and panel the 3 PCBs.
2020-07-08 Revert "updated ephys pcb with low profile connectors and started programming board"
2020-07-08 Remove paste on connector pads on ephys and connector PCB
2020-07-08 Switch spring connectors to a lower profile option
2020-07-08 Add programing board and generate GERBERS for fab (v0.1)
2020-07-16 Add all fab files for first PCB fab run of this design. v0.1 at PCBway.

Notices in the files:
parts and their libraries:
Copyright 2016 Accelerated Designs. All rights reserved.
